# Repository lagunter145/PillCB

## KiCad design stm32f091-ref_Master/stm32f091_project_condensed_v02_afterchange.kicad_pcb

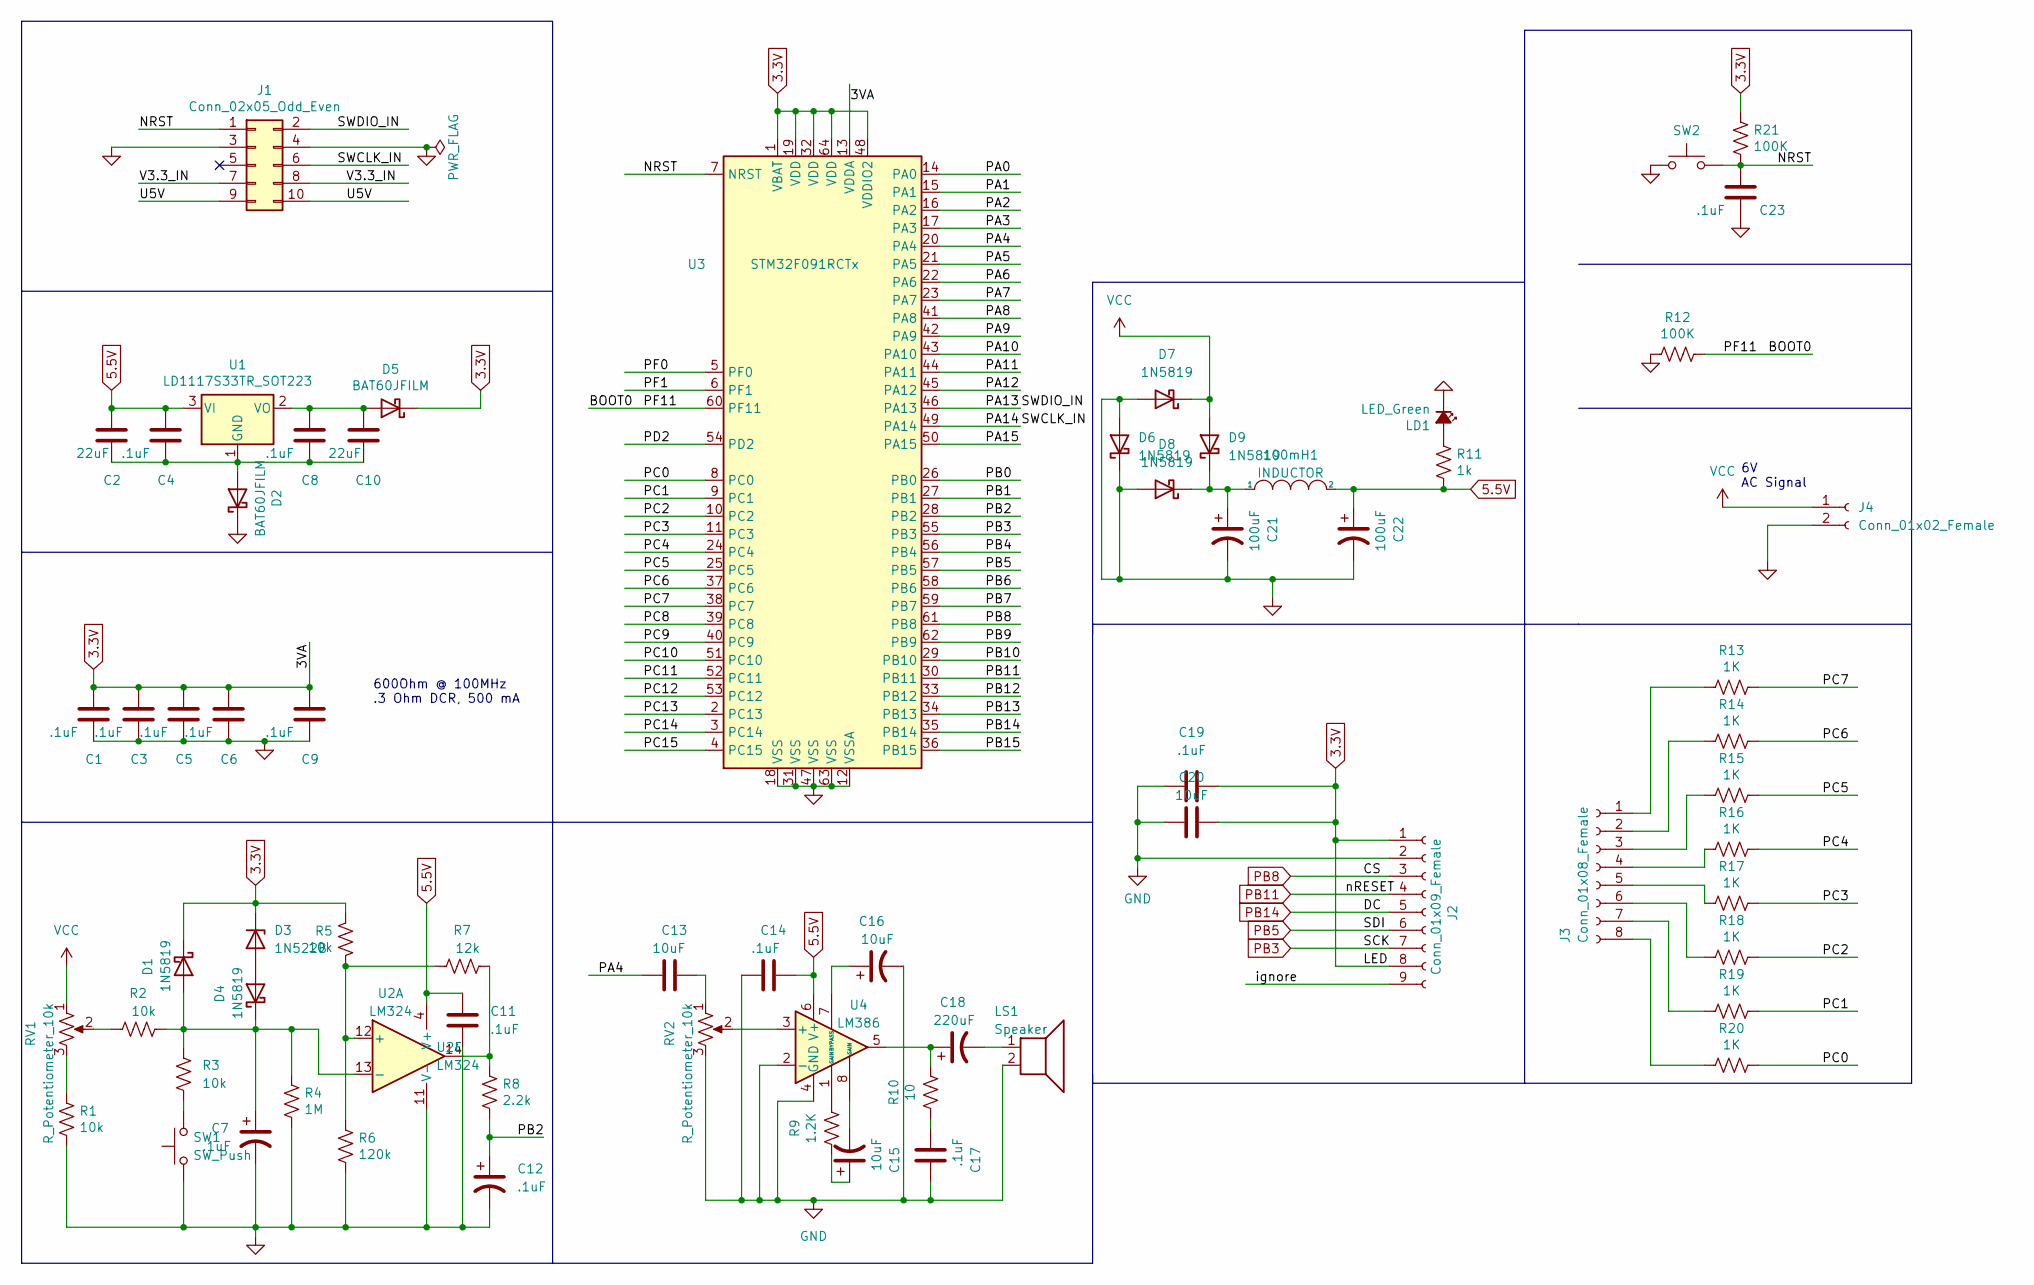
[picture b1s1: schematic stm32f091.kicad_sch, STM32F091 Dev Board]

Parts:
100mH1: INDUCTOR; L_Radial_D10.0mm_P5.00mm_Neosid_SD12_style3
C1, C3, C4, C5, C6, C7, C8, C9, C11, C12, C14, C17, C19, C23: .1uF; C_0805_2012Metric_Pad1.18x1.45mm_HandSolder
C2, C10: 22uF; C_0805_2012Metric_Pad1.18x1.45mm_HandSolder
C13, C15, C16, C20: 10uF; C_0805_2012Metric_Pad1.18x1.45mm_HandSolder
C18: 220uF; CP_Radial_D10.0mm_P5.00mm
C21, C22: 100uF; CP_Radial_D10.0mm_P5.00mm
D1, D4, D6, D7, D8, D9: 1N5819; D_DO-41_SOD81_P10.16mm_Horizontal
D2, D5: BAT60JFILM; D_SOD-323
D3: 1N522B; D_DO-41_SOD81_P10.16mm_Horizontal
J1: Conn_02x05_Odd_Even; IDC-Header_2x05_P2.54mm_Vertical
J2: Conn_01x09_Female; J3
J3: Conn_01x08_Female; J2
J4: Conn_01x02_Female; J1
LD1: LED_Green; LED_D2.0mm_W4.8mm_H2.5mm_FlatTop
LS1: Speaker; LS1
R1, R2, R3, R5: 10k; R_0805_2012Metric_Pad1.20x1.40mm_HandSolder
R4: 1M; R_0805_2012Metric_Pad1.20x1.40mm_HandSolder
R6: 120k; R_0805_2012Metric_Pad1.20x1.40mm_HandSolder
R7: 12k; R_0805_2012Metric_Pad1.20x1.40mm_HandSolder
R8: 2.2k; R_0805_2012Metric_Pad1.20x1.40mm_HandSolder
R9: 1.2K; R_0805_2012Metric_Pad1.20x1.40mm_HandSolder
R10: 10; R_0805_2012Metric_Pad1.20x1.40mm_HandSolder
R11: 1k; R_0805_2012Metric_Pad1.20x1.40mm_HandSolder
R12, R21: 100K; R_0805_2012Metric_Pad1.20x1.40mm_HandSolder
R13, R14, R15, R16, R17, R18, R19, R20: 1K; R_0805_2012Metric_Pad1.20x1.40mm_HandSolder
RV1, RV2: R_Potentiometer_10k; potentiometer
SW1, SW2: SW_Push; SW_SPST_PTS645
U1: LD1117S33TR_SOT223; SOT-223-3_TabPin2
U2: LM324; U2
U3: STM32F091RCTx; LQFP-64_10x10mm_P0.5mm
U4: LM386

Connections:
3.3V: C1.1, C3.1, C5.1, C6.1, C9.1, C19.1, C20.1, D1.1 (K), D3.1 (K), D5.1 (K), J2.1, J2.8, R5.1, R21.1, U3.1 (VBAT), U3.13 (VDDA), U3.19 (VDD), U3.32 (VDD), U3.48 (VDDIO2), U3.64 (VDD)
5.5V: 100mH1.2, C2.1, C4.1, C11.1, C14.2, C22.1, R11.2, U1.3 (VI), U2.4 (V+), U4.6 (V+)
/BOOT0: R12.1, U3.60 (PF11)
/NRST: C23.1, J1.1, R21.2, SW2.2, U3.7 (NRST)
/PA0: U3.14 (PA0)
/PA1: U3.15 (PA1)
/PA2: U3.16 (PA2)
/PA3: U3.17 (PA3)
/PA4: C13.1, U3.20 (PA4)
/PA5: U3.21 (PA5)
/PA6: U3.22 (PA6)
/PA7: U3.23 (PA7)
/PA8: U3.41 (PA8)
/PA9: U3.42 (PA9)
/PA10: U3.43 (PA10)
/PA11: U3.44 (PA11)
/PA12: U3.45 (PA12)
/PA13: J1.2, U3.46 (PA13)
/PA14: J1.6, U3.49 (PA14)
/PA15: U3.50 (PA15)
/PB0: U3.26 (PB0)
/PB1: U3.27 (PB1)
/PB2: C12.1, R8.2, U3.28 (PB2)
/PB4: U3.56 (PB4)
/PB6: U3.58 (PB6)
/PB7: U3.59 (PB7)
/PB9: U3.62 (PB9)
/PB10: U3.29 (PB10)
/PB12: U3.33 (PB12)
/PB13: U3.34 (PB13)
/PB15: U3.36 (PB15)
/PC0: R20.1, U3.8 (PC0)
/PC1: R19.1, U3.9 (PC1)
/PC2: R18.1, U3.10 (PC2)
/PC3: R17.1, U3.11 (PC3)
/PC4: R16.1, U3.24 (PC4)
/PC5: R15.1, U3.25 (PC5)
/PC6: R14.1, U3.37 (PC6)
/PC7: R13.1, U3.38 (PC7)
/PC8: U3.39 (PC8)
/PC9: U3.40 (PC9)
/PC10: U3.51 (PC10)
/PC11: U3.52 (PC11)
/PC12: U3.53 (PC12)
/PC13: U3.2 (PC13)
/PC14: U3.3 (PC14)
/PC15: U3.4 (PC15)
/PD2: U3.54 (PD2)
/PF0: U3.5 (PF0)
/PF1: U3.6 (PF1)
/U5V: J1.9, J1.10
/V3.3_IN: J1.7, J1.8
/ignore: J2.9
GND: C1.2, C3.2, C5.2, C6.2, C7.2, C9.2, C11.2, C12.2, C14.1, C16.2, C17.2, C19.2, C20.2, C21.2, C22.2, C23.2, D2.1 (K), D6.1 (K), D6.2 (A), D7.2 (A), D8.2 (A), J1.3, J1.4, J2.2, J4.2, LD1.1 (K), LS1.2, R1.2, R4.2, R6.2, R12.2, RV2.3, SW1.1, SW2.1, U2.11 (V-), U3.12 (VSSA), U3.18 (VSS), U3.31 (VSS), U3.47 (VSS), U3.63 (VSS), U4.2 (-), U4.4 (GND)
unnamed: 100mH1.1, C21.1, D8.1 (K), D9.1 (K)
unnamed: C7.1, D1.2 (A), D4.1 (K), R2.2, R3.1, R4.1, U2.13 (-)
unnamed: C8.1, C10.1, D5.2 (A), U1.2 (VO)
unnamed: C2.2, C4.2, C8.2, C10.2, D2.2 (A), U1.1 (GND)
unnamed: C13.2, RV2.1
unnamed: C15.1, R9.2
unnamed: C15.2, U4.8 (GAIN)
unnamed: C16.1, U4.7 (BYPASS)
unnamed: C17.1, R10.2
unnamed: C18.1, R10.1, U4.5
unnamed: C18.2, LS1.1
unnamed: D3.2 (A), D4.2 (A)
unnamed: J3.1, R13.2
unnamed: J3.2, R14.2
unnamed: J3.3, R15.2
unnamed: J3.4, R16.2
unnamed: J3.5, R17.2
unnamed: J3.6, R18.2
unnamed: J3.7, R19.2
unnamed: J3.8, R20.2
unnamed: LD1.2 (A), R11.1
unnamed: R1.1, RV1.3
unnamed: R2.1, RV1.2
unnamed: R3.2, SW1.2
unnamed: R5.2, R6.1, R7.1, U2.12 (+)
unnamed: R7.2, R8.1, U2.14
unnamed: R9.1, U4.1 (GAIN)
unnamed: RV2.2, U4.3 (+)
PB3: J2.7, U3.55 (PB3)
PB5: J2.6, U3.57 (PB5)
PB8: J2.3, U3.61 (PB8)
PB11: J2.4, U3.30 (PB11)
PB14: J2.5, U3.35 (PB14)
VCC: D7.1 (K), D9.2 (A), J4.1, RV1.1

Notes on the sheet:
600Ohm @ 100MHz .3 Ohm DCR, 500 mA
6V AC Signal

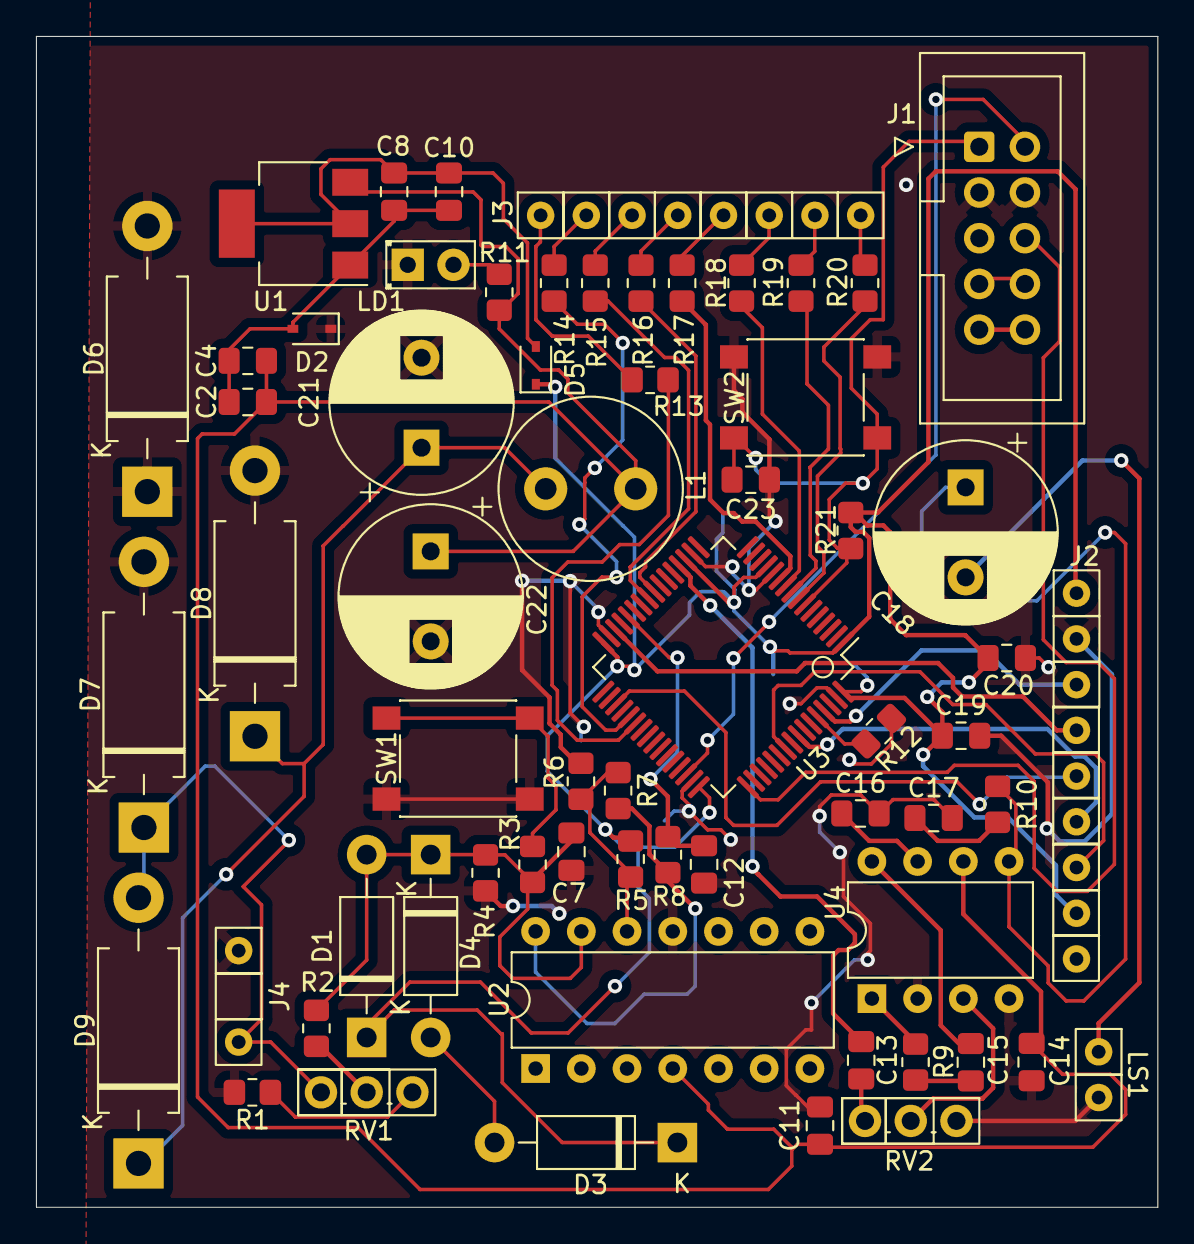
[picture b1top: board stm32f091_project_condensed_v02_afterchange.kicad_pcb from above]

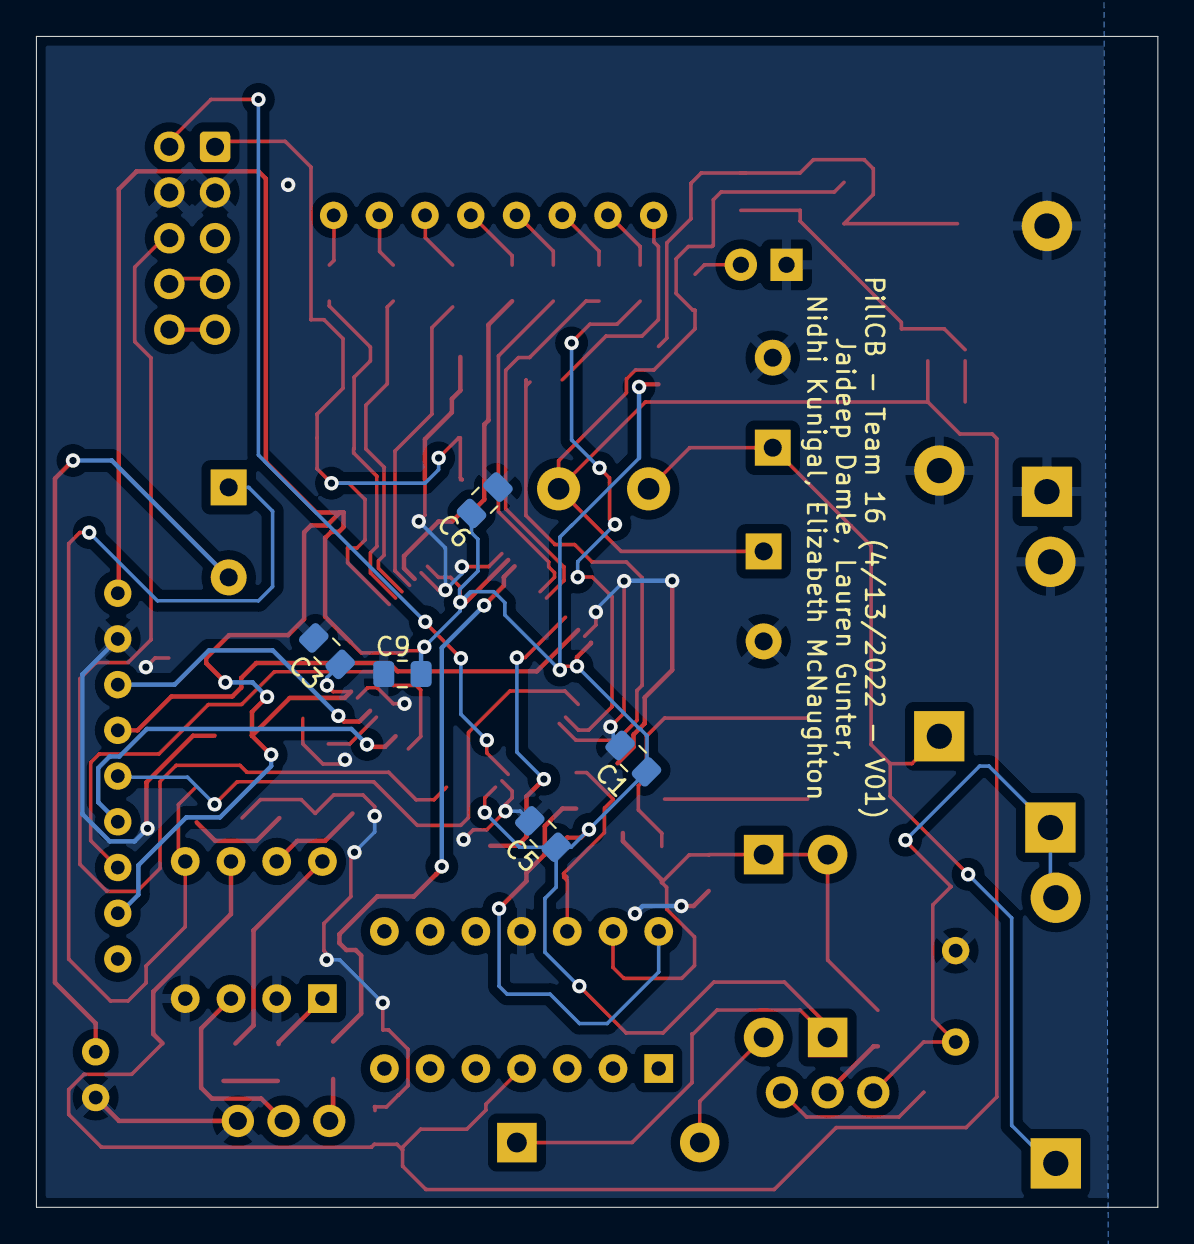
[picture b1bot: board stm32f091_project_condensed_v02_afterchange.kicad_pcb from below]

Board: 2 copper layers, 62.3 x 65.0 mm, 68 parts (5 on the bottom side), 53 nets.

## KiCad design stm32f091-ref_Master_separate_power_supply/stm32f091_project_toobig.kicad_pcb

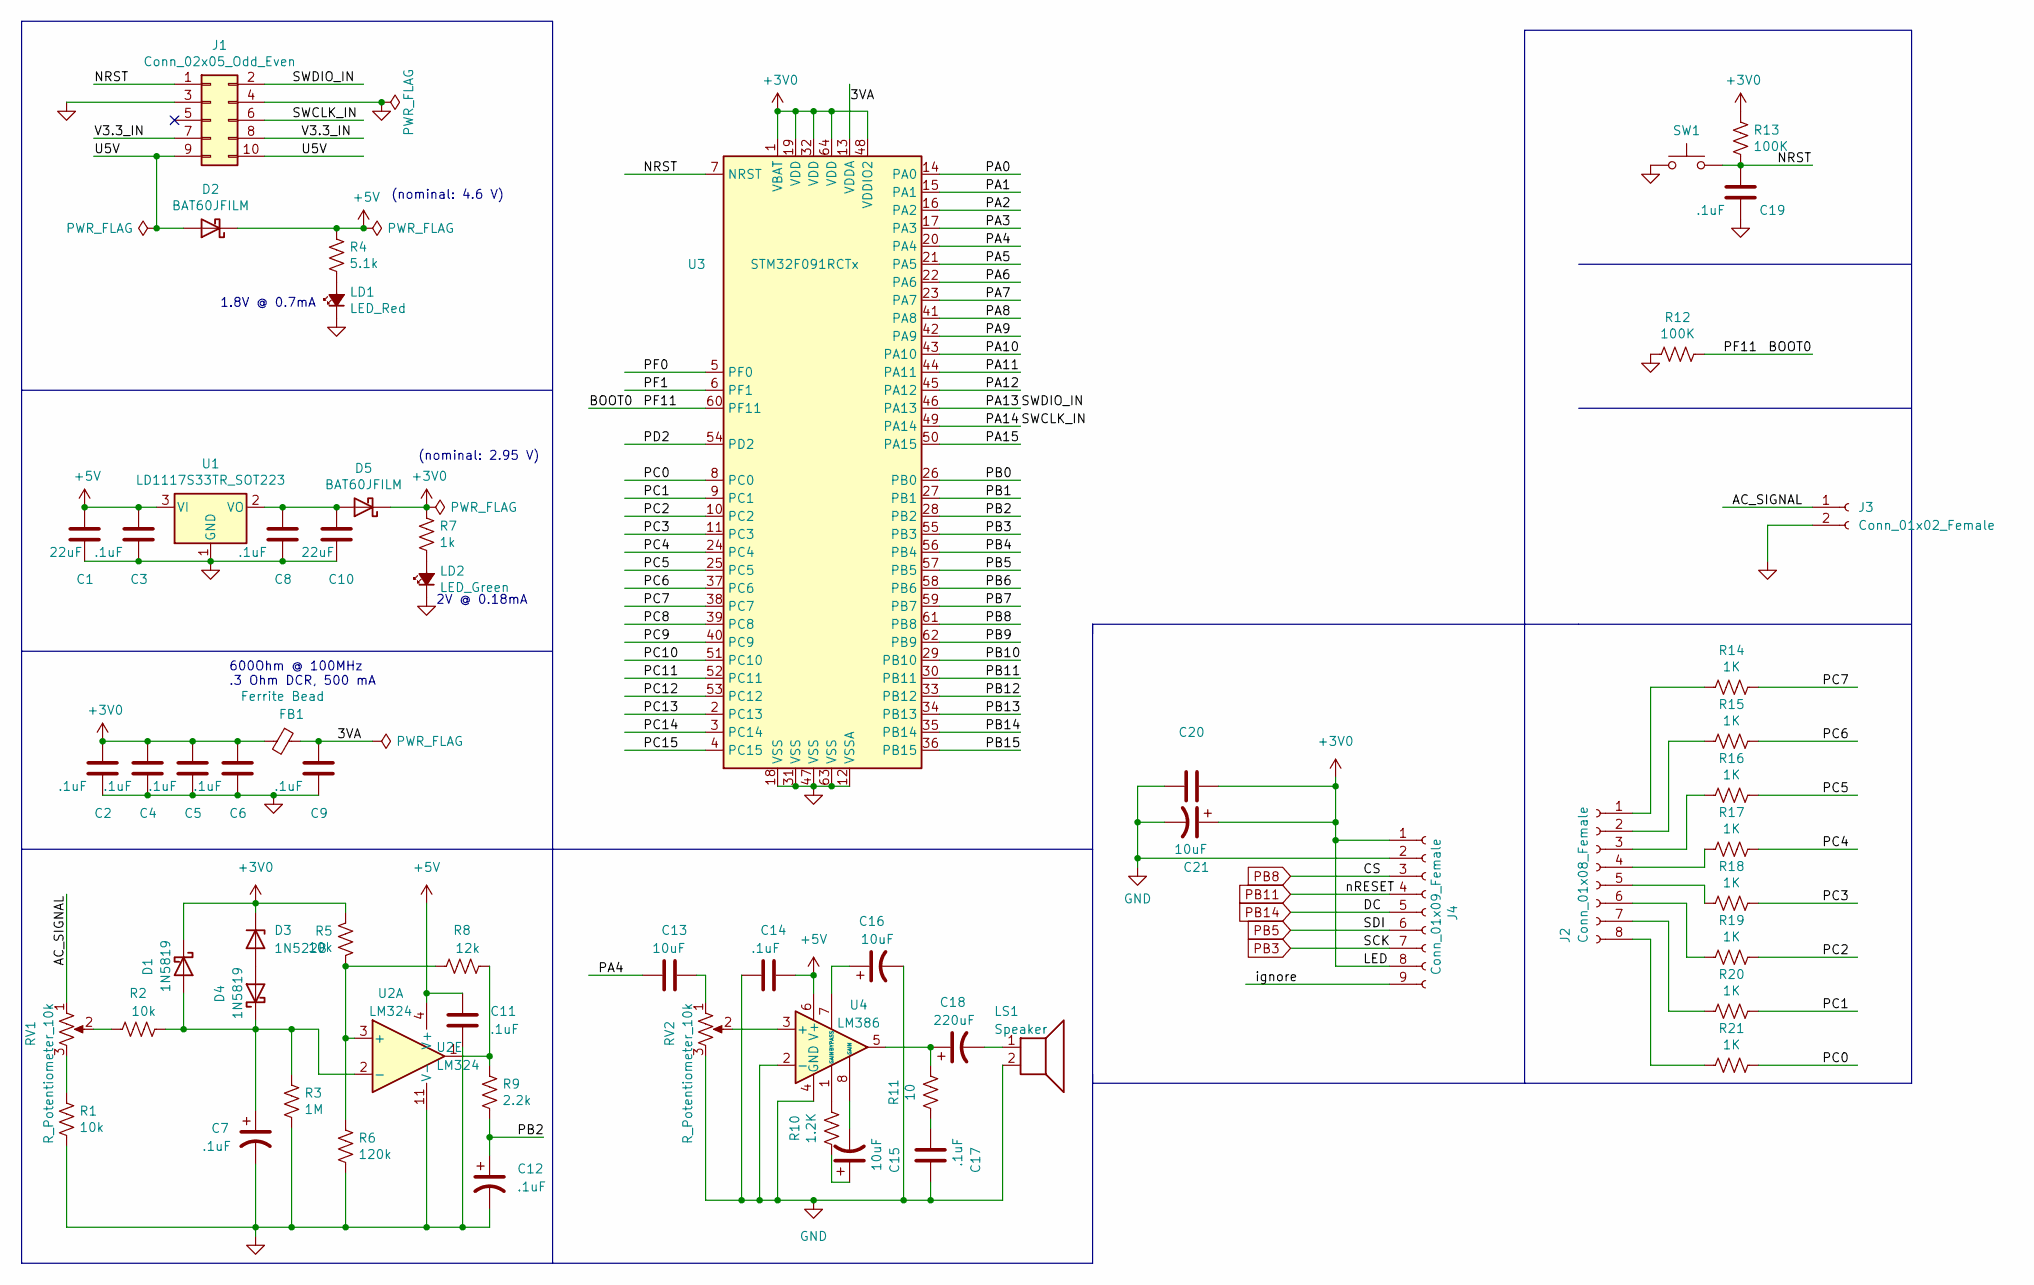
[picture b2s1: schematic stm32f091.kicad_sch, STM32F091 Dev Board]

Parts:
C1, C10: 22uF
C2, C3, C4, C5, C6, C7, C8, C9, C11, C12, C14, C17, C19: .1uF
C13, C15, C16, C21: 10uF
C18: 220uF
C20: (no value)
D1, D4: 1N5819; D_DO-41_SOD81_P10.16mm_Horizontal
D2, D5: BAT60JFILM; D_SOD-323
D3: 1N522B; D_DO-201_P15.24mm_Horizontal
FB1: Ferrite Bead; L_0805_2012Metric_Pad1.15x1.40mm_HandSolder
J1: Conn_02x05_Odd_Even; IDC-Header_2x05_P2.54mm_Vertical
J2: Conn_01x08_Female; J2
J3: Conn_01x02_Female; J1
J4: Conn_01x09_Female
LD1: LED_Red
LD2: LED_Green
LS1: Speaker; LS1
R1, R2, R5: 10k
R3: 1M
R4: 5.1k
R6: 120k
R7: 1k
R8: 12k
R9: 2.2k
R10: 1.2K
R11: 10
R12, R13: 100K
R14, R15, R16, R17, R18, R19, R20, R21: 1K
RV1, RV2: R_Potentiometer_10k; Potentiometer_Omeg_PC16BU_Vertical
SW1: SW_Push
U1: LD1117S33TR_SOT223; SOT-223-3_TabPin2
U2: LM324
U3: STM32F091RCTx; LQFP-64_10x10mm_P0.5mm
U4: LM386

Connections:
+3V0: C2.1, C4.1, C5.1, C6.1, C20.1, C21.1, D1.1 (K), D3.1 (K), D5.1 (K), FB1.2, J4.1, J4.8, R5.1, R7.1, R13.1, U3.1 (VBAT), U3.19 (VDD), U3.32 (VDD), U3.48 (VDDIO2), U3.64 (VDD)
+5V: C1.1, C3.1, C11.1, C14.2, D2.1 (K), R4.1, U1.3 (VI), U2.4 (V+), U4.6 (V+)
/3VA: C9.1, FB1.1, U3.13 (VDDA)
/AC_SIGNAL: J3.1, RV1.1
/BOOT0: R12.1, U3.60 (PF11)
/NRST: C19.1, J1.1, R13.2, SW1.2, U3.7 (NRST)
/PA0: U3.14 (PA0)
/PA1: U3.15 (PA1)
/PA2: U3.16 (PA2)
/PA3: U3.17 (PA3)
/PA4: C13.1, U3.20 (PA4)
/PA5: U3.21 (PA5)
/PA6: U3.22 (PA6)
/PA7: U3.23 (PA7)
/PA8: U3.41 (PA8)
/PA9: U3.42 (PA9)
/PA10: U3.43 (PA10)
/PA11: U3.44 (PA11)
/PA12: U3.45 (PA12)
/PA13: J1.2, U3.46 (PA13)
/PA14: J1.6, U3.49 (PA14)
/PA15: U3.50 (PA15)
/PB0: U3.26 (PB0)
/PB1: U3.27 (PB1)
/PB2: C12.1, R9.2, U3.28 (PB2)
/PB4: U3.56 (PB4)
/PB6: U3.58 (PB6)
/PB7: U3.59 (PB7)
/PB9: U3.62 (PB9)
/PB10: U3.29 (PB10)
/PB12: U3.33 (PB12)
/PB13: U3.34 (PB13)
/PB15: U3.36 (PB15)
/PC0: R21.1, U3.8 (PC0)
/PC1: R20.1, U3.9 (PC1)
/PC2: R19.1, U3.10 (PC2)
/PC3: R18.1, U3.11 (PC3)
/PC4: R17.1, U3.24 (PC4)
/PC5: R16.1, U3.25 (PC5)
/PC6: R15.1, U3.37 (PC6)
/PC7: R14.1, U3.38 (PC7)
/PC8: U3.39 (PC8)
/PC9: U3.40 (PC9)
/PC10: U3.51 (PC10)
/PC11: U3.52 (PC11)
/PC12: U3.53 (PC12)
/PC13: U3.2 (PC13)
/PC14: U3.3 (PC14)
/PC15: U3.4 (PC15)
/PD2: U3.54 (PD2)
/PF0: U3.5 (PF0)
/PF1: U3.6 (PF1)
/U5V: D2.2 (A), J1.9, J1.10
/V3.3_IN: J1.7, J1.8
/ignore: J4.9
GND: C1.2, C2.2, C3.2, C4.2, C5.2, C6.2, C7.2, C8.2, C9.2, C10.2, C11.2, C12.2, C14.1, C16.2, C17.2, C19.2, C20.2, C21.2, J1.3, J1.4, J3.2, J4.2, LD1.1 (K), LD2.1 (K), LS1.2, R1.2, R3.2, R6.2, R12.2, RV2.3, SW1.1, U1.1 (GND), U2.11 (V-), U3.12 (VSSA), U3.18 (VSS), U3.31 (VSS), U3.47 (VSS), U3.63 (VSS), U4.2 (-), U4.4 (GND)
unnamed: C7.1, D1.2 (A), D4.1 (K), R2.2, R3.1, U2.2 (-)
unnamed: C8.1, C10.1, D5.2 (A), U1.2 (VO)
unnamed: C13.2, RV2.1
unnamed: C15.1, R10.2
unnamed: C15.2, U4.8 (GAIN)
unnamed: C16.1, U4.7 (BYPASS)
unnamed: C17.1, R11.2
unnamed: C18.1, R11.1, U4.5
unnamed: C18.2, LS1.1
unnamed: D3.2 (A), D4.2 (A)
unnamed: J2.1, R14.2
unnamed: J2.2, R15.2
unnamed: J2.3, R16.2
unnamed: J2.4, R17.2
unnamed: J2.5, R18.2
unnamed: J2.6, R19.2
unnamed: J2.7, R20.2
unnamed: J2.8, R21.2
unnamed: LD1.2 (A), R4.2
unnamed: LD2.2 (A), R7.2
unnamed: R1.1, RV1.3
unnamed: R2.1, RV1.2
unnamed: R5.2, R6.1, R8.1, U2.3 (+)
unnamed: R8.2, R9.1, U2.1
unnamed: R10.1, U4.1 (GAIN)
unnamed: RV2.2, U4.3 (+)
PB3: J4.7, U3.55 (PB3)
PB5: J4.6, U3.57 (PB5)
PB8: J4.3, U3.61 (PB8)
PB11: J4.4, U3.30 (PB11)
PB14: J4.5, U3.35 (PB14)

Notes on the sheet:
600Ohm @ 100MHz .3 Ohm DCR, 500 mA
(nominal: 4.6 V)
2V @ 0.18mA
(nominal: 2.95 V)
1.8V @ 0.7mA

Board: 4 copper layers, 62 parts (0 on the bottom side), 52 nets, no tracks yet.

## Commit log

2022-04-03 added hw8 (display)
2022-04-04 Added proposal to github
2022-04-04 Wrapped text for proposal
2022-04-06 adding midi song file
2022-04-06 trying to convert midi file to char array
2022-04-07 took out midi to char algorithm
2022-04-11 Added KiCad project files
2022-04-11 copied kiCad project for each person so we can do simultaneous work easier
2022-04-11 added a master kiCad file to allow us to combine our pieces of the design
2022-04-12 added clock circuit
2022-04-12 drew kicad schematic for keypad and speaker circuit
2022-04-13 schematic for circuit with separate power supply with appropriate footprints of netlist
2022-04-13 PCB designs w/out traces for a regular and condensed PCB
2022-04-14 changed r's and c's to SM in condensed PCB design
2022-04-14 copied files from master_separate_power_supply to master
2022-04-15 new pcb with the traces
2022-04-16 schematic and netlist with AC-DC circuits added
2022-04-17 v02 pcb with front tracings
2022-04-18 new pcb design
2022-04-18 minor tracing changes and edge cut added for v02 pcb
2022-04-18 added gerber files for current v02 design to get quotes
2022-04-18 rick's changes, still need to swap out ic footprints
2022-04-19 new pcb after diode and 324 changes
2022-04-19 changed silkscreen to not overlap (no warnings) and created gerber files (plot_v02_approved)
2022-04-21 Create newclockcode.txt
    new clock code
2022-04-21 Create clockcodwithworkingcountdown.txt
    new clock code with the countdowns working
2022-04-21 files added for pill dancing animation
2022-04-22 Create Pirates of the Caribbean - He's a Pirate (1) (1).mid
    drink up me hearties, yo ho!
2022-04-22 converted midi file of chosen song to array
2022-04-22 Create clockcodeworkingcountdownthenewversion.txt
    new stuff we just did
2022-04-22 Lizzie's code
    Lizzie's code
2022-04-22 testing for nidhi
2022-04-22 Create clockpt3.txt
    clockpt3
2022-04-22 Add files via upload
    most recent clock code
2022-04-24 updated main.c with all pill countdowns
2022-04-24 updated screen.c with all pill countdowns
2022-04-25 Create screen3.c
    added synchronization
2022-04-25 Create main4.c
    switching between screens / keypad stuff works
2022-04-25 made smaller versions of the animation pictures
2022-04-26 added code for animation
2022-04-26 testing new animation file
2022-04-26 Create screen5.c
    new screen.c
2022-04-26 Create main5.c
    new main.c
2022-04-26 Create keypad5.c
    new keypad.c
2022-04-26 Create main6.c
    updated main.c
2022-04-26 Create screen7.c
    updated screen.c
2022-04-27 updated main.c
2022-04-27 screen8.c
2022-04-27 updated keypad8.c
2022-04-28 project code from laurens computer
2022-04-29 fixed fast mode to work on only timer and animation
2022-04-29 Update screen.c
    fixed boo-boo with minutes increasing in fast mode
2022-04-29 Delete clockcodwithworkingcountdown.c
    bye bye
2022-04-29 added code to show time as the user is inputting
